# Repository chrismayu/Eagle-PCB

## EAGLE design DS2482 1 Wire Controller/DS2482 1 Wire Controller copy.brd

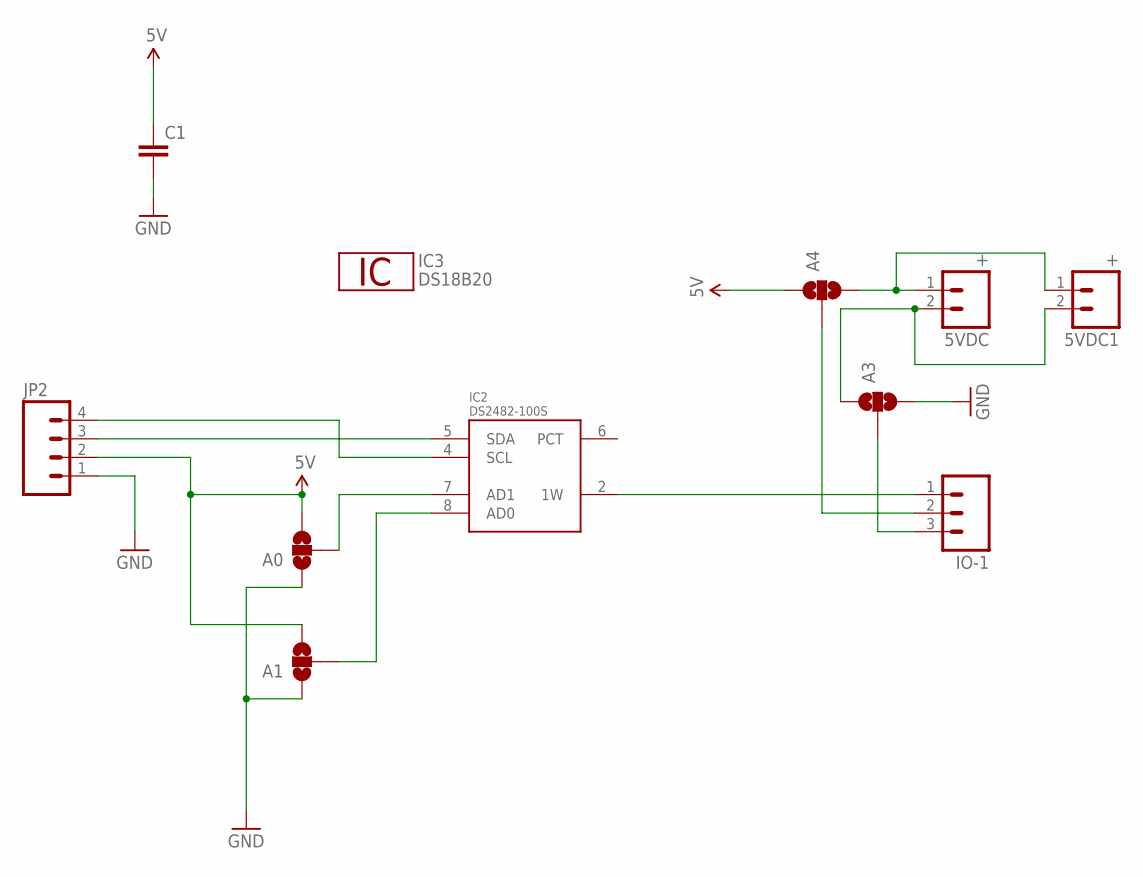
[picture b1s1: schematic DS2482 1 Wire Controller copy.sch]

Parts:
5VDC, 5VDC1: +; 1X02
A0, A1, A3, A4: SOLDERJUMPER_2WAYS; SJ_3
C1: CAPPTH2; CAP-PTH-SMALL2
IC2: DS2482-100S; SO08
IC3: DS18B20; TO92-
IO-1: M03PTH; 1X03
JP2: M04PTH; 1X04

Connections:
1W: IC3.2 (1W)
5V: A0.3, A1.3, A4.1, C1.1, JP2.2
GND: A0.1, A1.1, A3.3, C1.2, IC2.3 (GND), IC3.1 (GND), JP2.1
unnamed: IC2.2 (1W), IO-1.1
unnamed: IC2.4 (SCL), JP2.4
unnamed: A0.2, IC2.7 (AD1)
unnamed: IC2.5 (SDA), JP2.3
unnamed: A3.2, IO-1.3
unnamed: A1.2, IC2.8 (AD0)
unnamed: A4.2, IO-1.2
unnamed: 5VDC.1, 5VDC1.1, A4.3
unnamed: 5VDC.2, 5VDC1.2, A3.1
VDD: IC2.1 (VDD), IC3.3 (VDD)

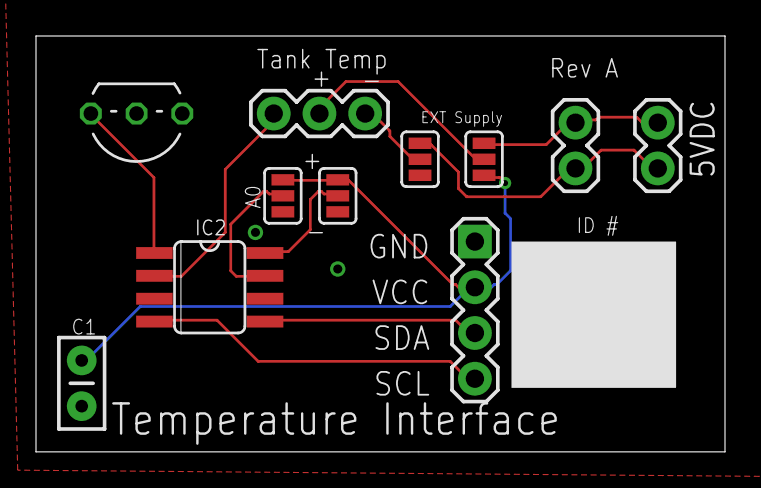
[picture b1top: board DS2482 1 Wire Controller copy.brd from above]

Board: 2 copper layers, 38.3 x 23.1 mm, 11 parts (0 on the bottom side), 12 nets.

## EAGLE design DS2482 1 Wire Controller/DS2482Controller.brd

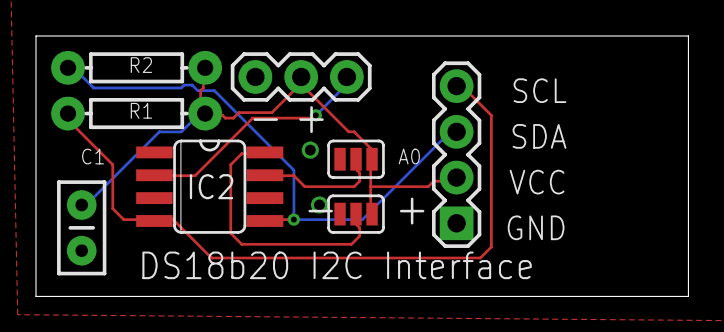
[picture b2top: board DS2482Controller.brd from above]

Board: 2 copper layers, 36.2 x 14.5 mm, 8 parts (0 on the bottom side), 7 nets.

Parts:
A0, A1: SJ_3
C1: CAP-PTH-SMALL2
IC2: DS2482-100S; SO08
JP2: 1X04
JP4: 1X03
R1, R2: 2.2k; AXIAL-0.3

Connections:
5V: A0.3, A1.3, C1.1, JP2.2, JP4.2, R1.P$2, R2.P$2
GND: A0.1, A1.1, C1.2, IC2.3, JP2.1, JP4.3
unnamed: A0.2, IC2.7
unnamed: IC2.4, JP2.4, R1.P$1
unnamed: IC2.5, JP2.3, R2.P$1
unnamed: A1.2, IC2.8
unnamed: IC2.2, JP4.1

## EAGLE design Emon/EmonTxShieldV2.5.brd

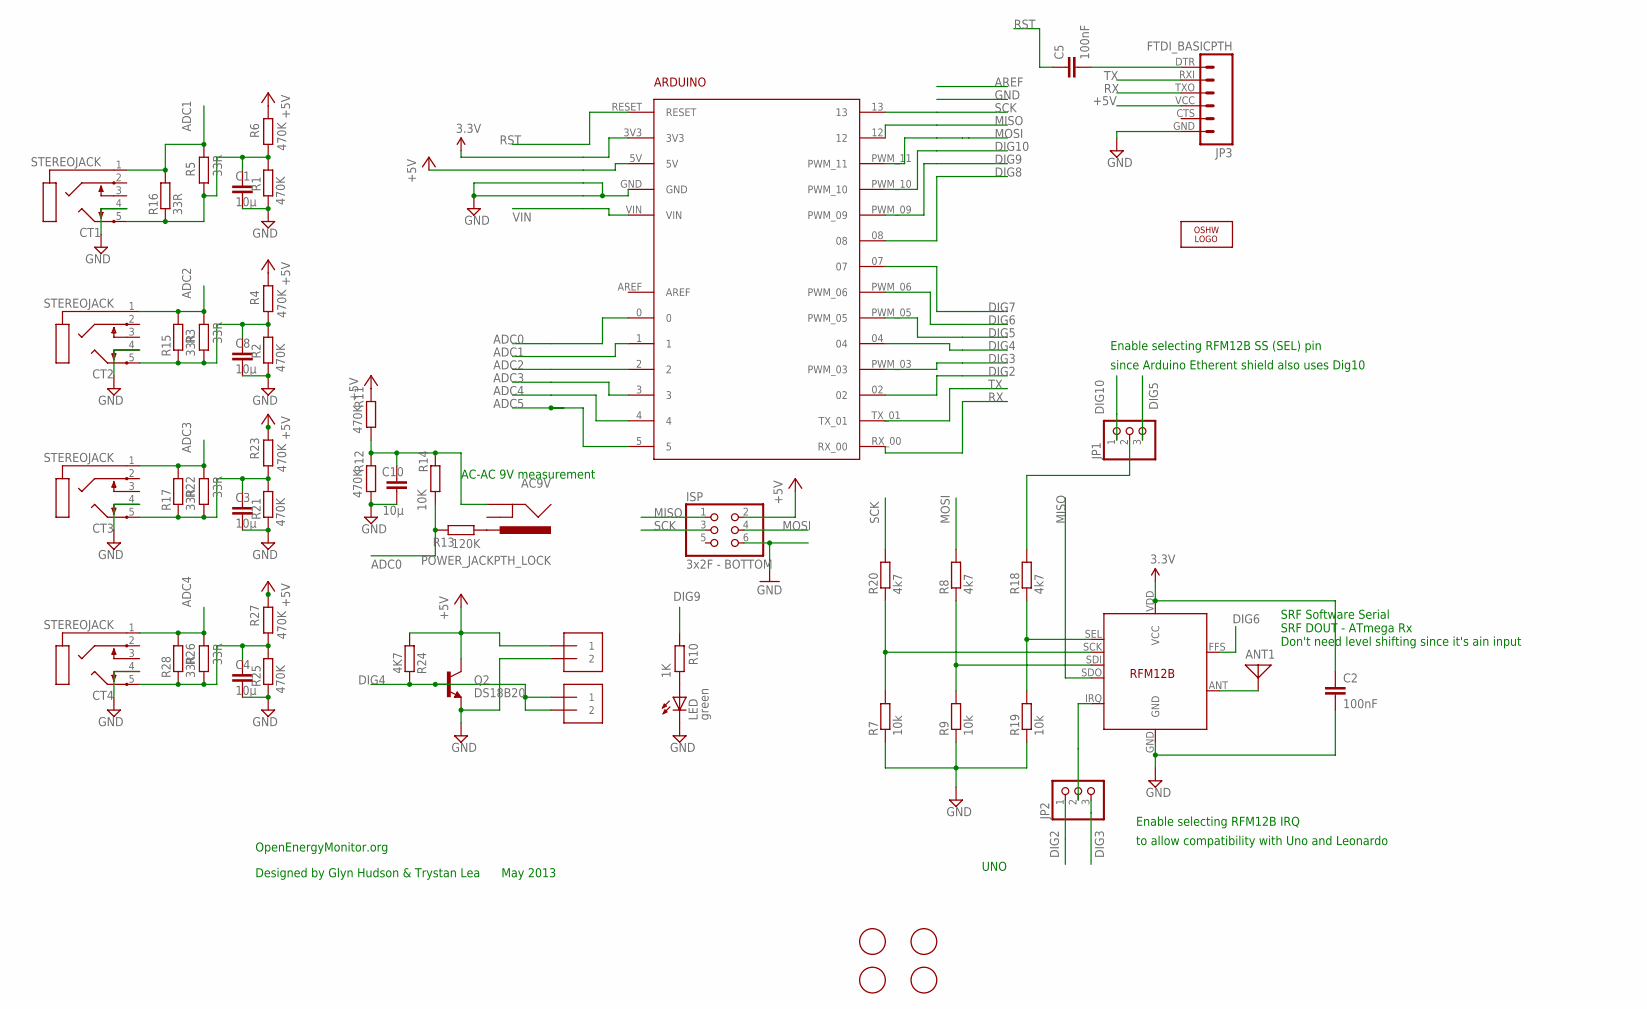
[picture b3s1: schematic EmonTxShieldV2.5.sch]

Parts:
AC9V: POWER_JACKPTH_LOCK; POWER_JACK_PTH_LOCK
ANT1: ANTENNA; PAD-01
ARDUINO1: ARDUINO2
C1, C3, C4, C8, C10: 10µ; C0603
C2, C5: 100nF; C0603
CT1, CT2, CT3, CT4: STEREOJACK; STX3100
ISP: 3x2F - BOTTOM; 2X03
J1, J2: 1X2-3.5MM
JP1, JP2: PINHD-1X3; 1X03
JP3: FTDI_BASICPTH; FTDI_BASIC
LED: green; CHIPLED_0805
LOGO1: OSHW_LOGO_10MILX0200-NT; OSHW_10X200_NOTEXT
Q2: DS18B20; TO-92
R1, R2, R4, R6, R11, R12, R21, R23, R25, R27: 470K; R0603
R3, R5, R22, R26: 33R; 0204/7
R7, R9, R19: 10k; R0603
R8, R18, R20: 4k7; R0603
R10: 1K; R0603
R13: 120K; R0603
R14: 10K; R0603
R15, R16, R17, R28: 33R; R1206
R24: 4K7; R0603
U$1, U$3, U$4, U$5: FIDUCIAL; FIDUCIAL_1MM
U$2: RFM12B

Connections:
3.3V: ARDUINO1.3V3, C2.1, U$2.VDD (VCC)
+5V: ARDUINO1.5V, ISP.2, J1.1, JP3.VCC (4), Q2.3 (C), R4.2, R6.2, R11.2, R23.2, R24.1, R27.2
ADC0: ARDUINO1.0, R13.2, R14.1
ADC1: ARDUINO1.1, CT1.1, R5.2, R16.2
ADC2: ARDUINO1.2, CT2.1, R3.2, R15.2
ADC3: ARDUINO1.3, CT3.1, R17.2, R22.2
ADC4: ARDUINO1.4, CT4.1, R26.2, R28.2
ADC5: ARDUINO1.5
DIG2: ARDUINO1.02, JP2.1
DIG3: ARDUINO1.PWM_03, JP2.3
DIG4: ARDUINO1.04, J2.1, J2.2, Q2.2 (B), R24.2
DIG5: ARDUINO1.PWM_05, JP1.3
DIG6: ARDUINO1.PWM_06, U$2.FFS
DIG7: ARDUINO1.07
DIG8: ARDUINO1.08
DIG9: ARDUINO1.PWM_09, R10.2
DIG10: ARDUINO1.PWM_10, JP1.1
GND: ARDUINO1.GND, C1.2, C2.2, C3.2, C4.2, C8.2, C10.2, CT1.4, CT2.4, CT3.4, CT4.4, ISP.6, J1.2, JP3.GND (6), LED.C, Q2.1 (E), R1.2, R2.2, R7.1, R9.1, R12.1, R19.1, R21.2, R25.2, U$2.GND
MISO: ARDUINO1.12, ISP.1, U$2.SDO
MOSI: ARDUINO1.PWM_11, ISP.4, R8.2
unnamed: JP2.2, U$2.IRQ
unnamed: JP1.2, R18.2
unnamed: C3.1, CT3.5, R17.1, R21.1, R22.1, R23.1
unnamed: C4.1, CT4.5, R25.1, R26.1, R27.1, R28.1
unnamed: AC9V.PWR, R13.1
unnamed: C5.2, JP3.DTR (1)
unnamed: C8.1, CT2.5, R2.1, R3.1, R4.1, R15.1
unnamed: AC9V.GND, C10.1, R11.1, R12.2, R14.2
unnamed: C1.1, CT1.5, R1.1, R5.1, R6.1, R16.1
unnamed: LED.A, R10.1
unnamed: ANT1.1, U$2.ANT
unnamed: R7.2, R20.1, U$2.SCK
unnamed: R8.1, R9.2, U$2.SDI
unnamed: R18.1, R19.2, U$2.SEL
RST: ARDUINO1.RESET, C5.1
RX: ARDUINO1.RX_00, JP3.TXO (3)
SCK: ARDUINO1.13, ISP.3, R20.2
TX: ARDUINO1.TX_01, JP3.RXI (2)
VIN: ARDUINO1.VIN

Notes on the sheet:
AC-AC 9V measurement
Enable selecting RFM12B SS (SEL) pin
since Arduino Etherent shield also uses Dig10
Enable selecting RFM12B IRQ
to allow compatibility with Uno and Leonardo
UNO
OpenEnergyMonitor.org
Designed by Glyn Hudson & Trystan Lea May 2013
SRF Software Serial SRF DOUT - ATmega Rx Don't need level shifting since it's ain input

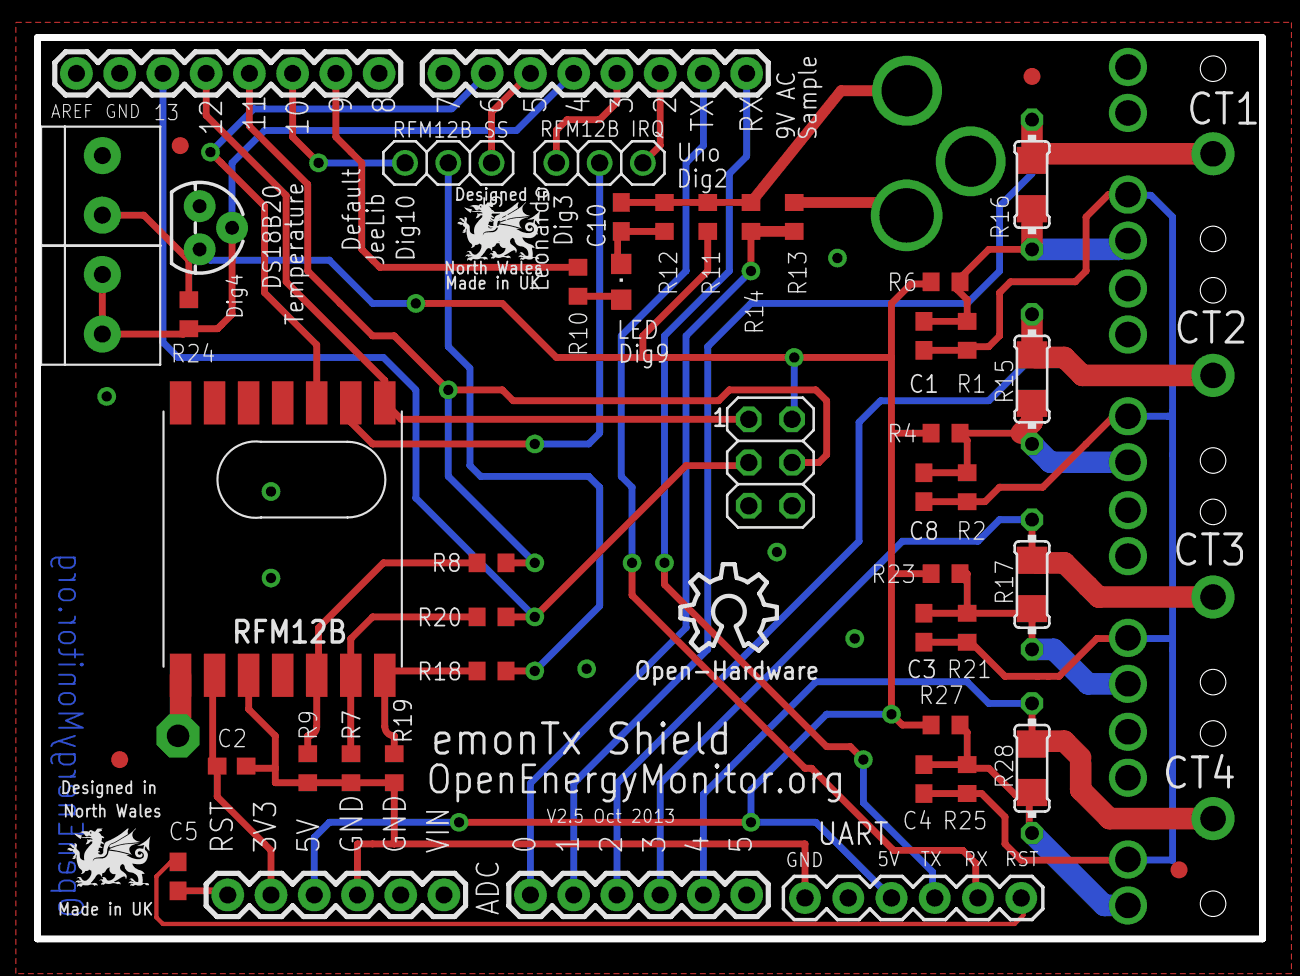
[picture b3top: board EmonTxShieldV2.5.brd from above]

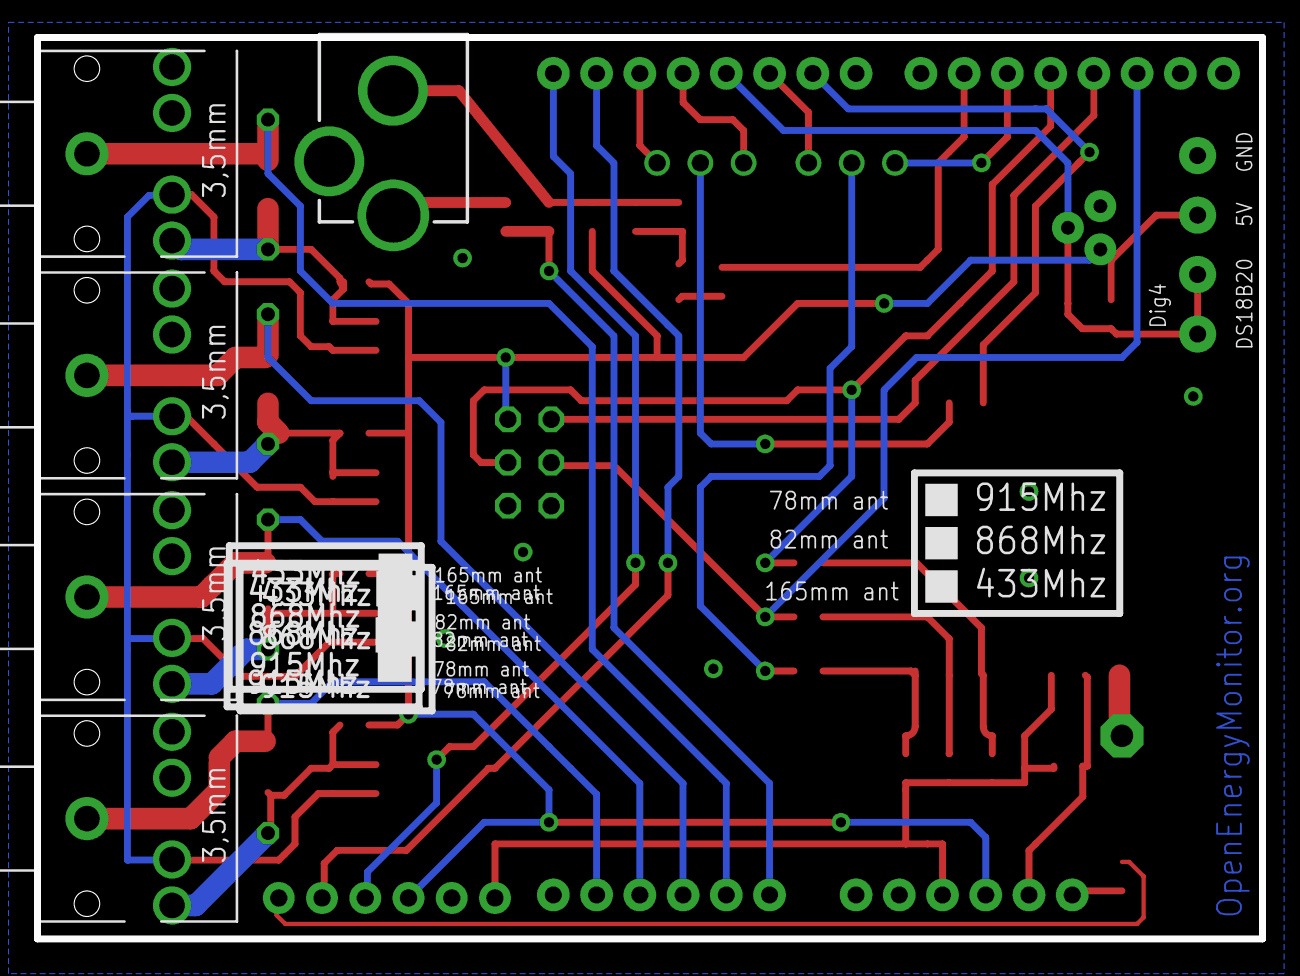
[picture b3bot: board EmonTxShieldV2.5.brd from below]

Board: 2 copper layers, 72.0 x 53.0 mm, 56 parts (5 on the bottom side), 35 nets.

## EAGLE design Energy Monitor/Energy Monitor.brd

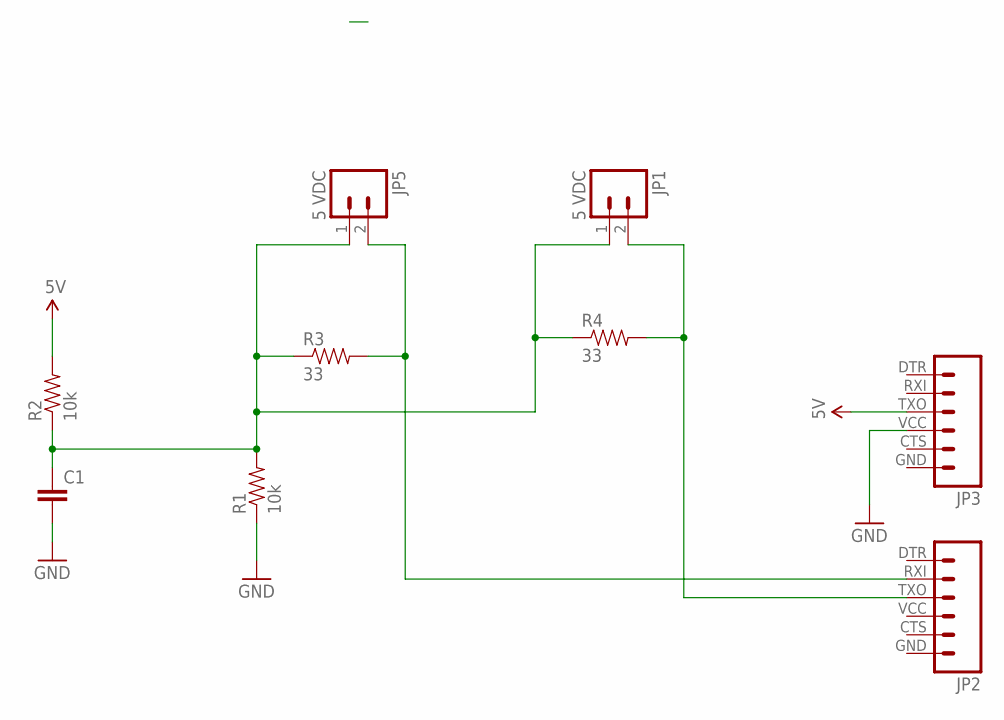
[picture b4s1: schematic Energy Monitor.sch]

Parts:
C1: CAPPTH2; CAP-PTH-SMALL2
JP1, JP5: 5 VDC; SCREWTERMINAL-5MM-2
JP2, JP3: M06SIP; 1X06
R1, R2: 10k; AXIAL-0.3
R3, R4: 33; AXIAL-0.3

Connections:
5V: JP3.TXO (3), R2.P$2 (2)
GND: C1.2, JP3.VCC (4), R1.P$1 (1)
unnamed: C1.1, JP1.1, JP5.1, R1.P$2 (2), R2.P$1 (1), R3.P$1 (1), R4.P$1 (1)
unnamed: JP1.2, JP2.TXO (3), R4.P$2 (2)
unnamed: JP2.RXI (2), JP5.2, R3.P$2 (2)

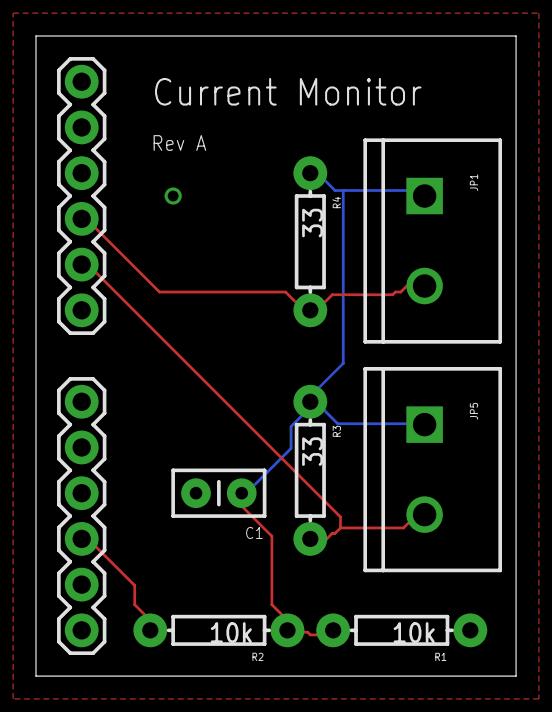
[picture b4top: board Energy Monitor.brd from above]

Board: 2 copper layers, 26.7 x 35.6 mm, 9 parts (0 on the bottom side), 5 nets.

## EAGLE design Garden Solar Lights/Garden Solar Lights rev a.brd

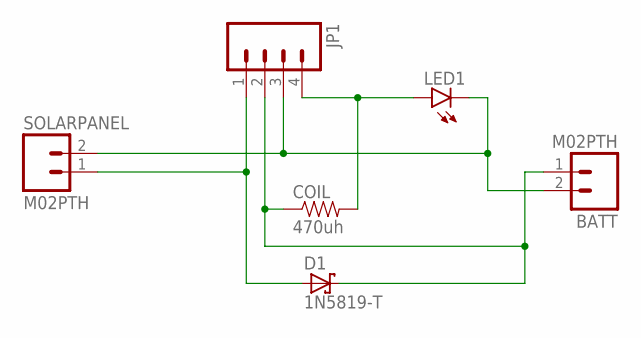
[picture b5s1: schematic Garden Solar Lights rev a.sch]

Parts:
BATT: M02PTH; 1X02
COIL: 470uh; AXIAL-0.5
D1: 1N5819-T; DO41-7.6
JP1: M04PTH; 1X04
LED1: LED3MM
SOLARPANEL: M02PTH; 1X02

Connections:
unnamed: D1.A, JP1.1, SOLARPANEL.1
unnamed: BATT.1, COIL.P$1 (1), D1.C, JP1.2
unnamed: COIL.P$2 (2), JP1.4, LED1.A
unnamed: BATT.2, JP1.3, LED1.K (C), SOLARPANEL.2

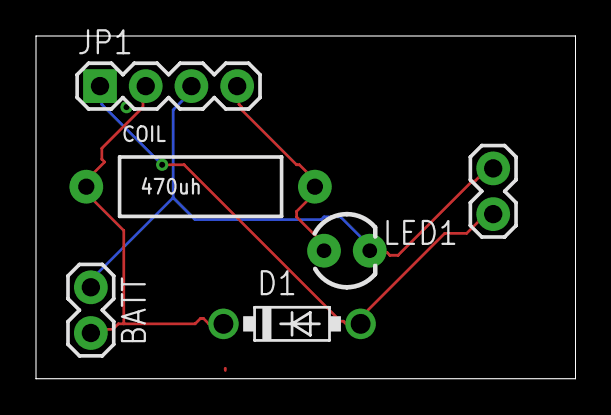
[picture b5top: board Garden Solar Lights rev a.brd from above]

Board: 2 copper layers, 30.0 x 19.0 mm, 6 parts (0 on the bottom side), 4 nets.

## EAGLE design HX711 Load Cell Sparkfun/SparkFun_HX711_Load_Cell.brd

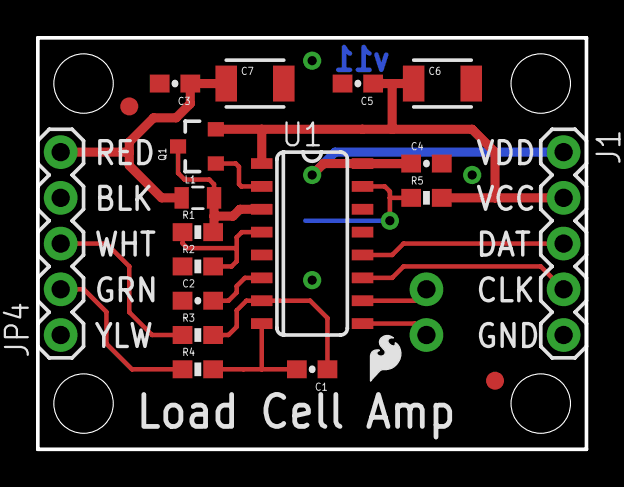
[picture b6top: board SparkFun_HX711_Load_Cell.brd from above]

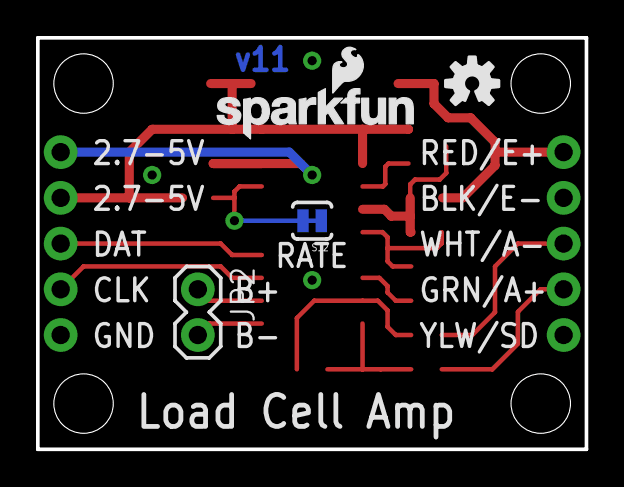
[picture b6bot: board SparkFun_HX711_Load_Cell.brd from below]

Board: 2 copper layers, 30.5 x 22.9 mm, 30 parts (4 on the bottom side), 17 nets.

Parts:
C1, C2, C3, C4, C5: 0.1uF; 0603-CAP
C6, C7: 10uF; 1210
FID1, FID2: FIDUCIAL1X2; FIDUCIAL-1X2
FRAME1: FRAME-LETTER; CREATIVE_COMMONS
J1: 1X05
JP2: 1X02
JP4: 1X05
L1: 3.3uH; 0805
LOGO1: SFE_LOGO_NAME_FLAME.1_INCH; SFE_LOGO_NAME_FLAME_.1
LOGO3: SFE_LOGO_FLAME.1_INCH; SFE_LOGO_FLAME_.1
Q1: MMBT4403; SOT23-3
R1: 20k; 0603-RES
R2: 8.2K; 0603-RES
R3, R4: 100; 0603-RES
R5: 10K; 0603-RES
SJ2: PAD-JUMPER-2-NC_BY_TRACE_YES_SILK
STANDOFF1, STANDOFF2, STANDOFF3, STANDOFF4: STAND-OFF
U1: HX711; SO16
U7: OSHW-LOGOS; OSHW-LOGO-S
U$1: REVISION

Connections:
A+: JP4.2, R4.1
A-: JP4.3, R3.1
AVDD: C3.1, C7.1, JP4.5, L1.1
B+: JP2.1, U1.10
B-: JP2.2, U1.9
DAT: J1.3, U1.12
GND: C2.1, C3.2, C4.2, C5.2, C6.2, C7.2, J1.5, JP4.1, JP4.4, R2.1, SJ2.1, U1.5, U1.14
unnamed: R5.1, SJ2.2, U1.15
unnamed: C1.1, R3.2, U1.7
unnamed: C1.2, R4.2, U1.8
unnamed: Q1.1, U1.2
unnamed: L1.2, Q1.3, R1.2, U1.3
unnamed: R1.1, R2.2, U1.4
unnamed: C2.2, U1.6
SCK: J1.4, U1.11
VCC: C5.1, C6.1, J1.2, Q1.2, R5.2, U1.1
VDD: C4.1, J1.1, U1.16

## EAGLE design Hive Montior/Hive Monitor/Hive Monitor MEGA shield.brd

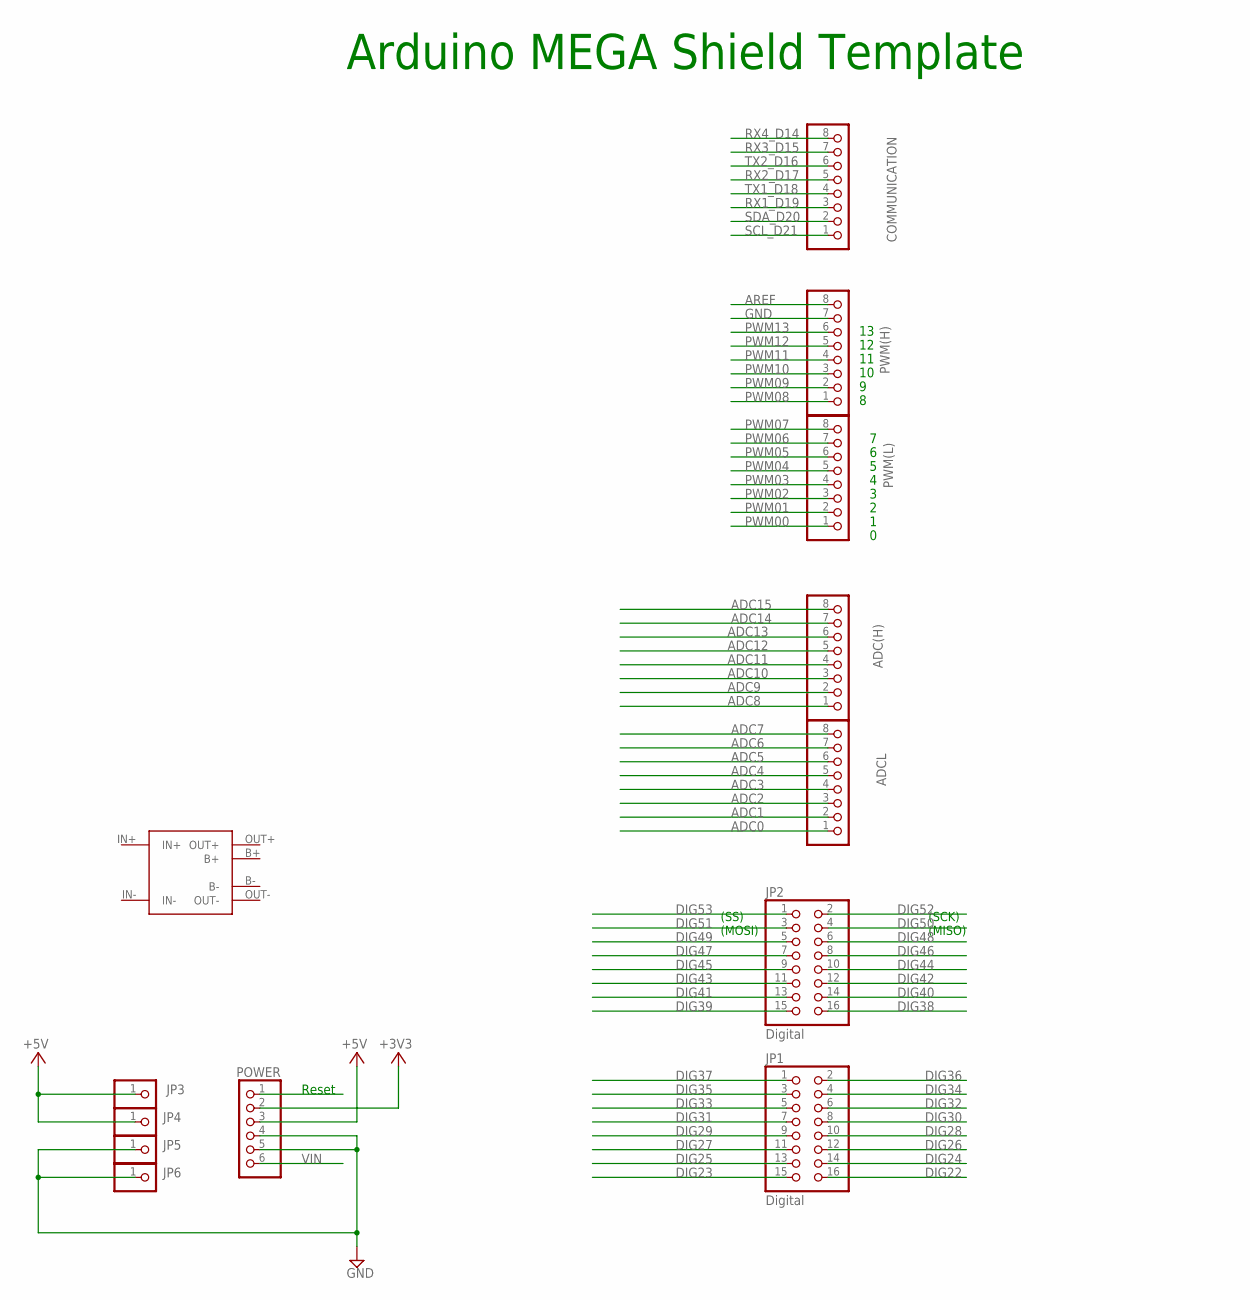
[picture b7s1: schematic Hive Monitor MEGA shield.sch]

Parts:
ADC(H): PINHD-1X8; 1X08
ADCL: PINHD-1X8; 1X08
COMMUNICATION: PINHD-1X8; 1X08
JP1, JP2: Digital; 2X08
JP3, JP4, JP5, JP6: PINHD-1X1; 1X01
POWER: PINHD-1X6; 1X06
PWM(H): PINHD-1X8; 1X08
PWM(L): PINHD-1X8; 1X08
U$1: TP4056-MODULE; TP4056-LITHIUM-PROTECTED-MODULE

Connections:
+3V3: POWER.2
+5V: JP3.1, JP4.1, POWER.3
ADC0: ADCL.1
ADC1: ADCL.2
ADC2: ADCL.3
ADC3: ADCL.4
ADC4: ADCL.5
ADC5: ADCL.6
ADC6: ADCL.7
ADC7: ADCL.8
ADC8: ADC(H).1
ADC9: ADC(H).2
ADC10: ADC(H).3
ADC11: ADC(H).4
ADC12: ADC(H).5
ADC13: ADC(H).6
ADC14: ADC(H).7
ADC15: ADC(H).8
AREF: PWM(H).8
B+: U$1.B+
B-: U$1.B-
DIG22: JP1.16
DIG23: JP1.15
DIG24: JP1.14
DIG25: JP1.13
DIG26: JP1.12
DIG27: JP1.11
DIG28: JP1.10
DIG29: JP1.9
DIG30: JP1.8
DIG31: JP1.7
DIG32: JP1.6
DIG33: JP1.5
DIG34: JP1.4
DIG35: JP1.3
DIG36: JP1.2
DIG37: JP1.1
DIG38: JP2.16
DIG39: JP2.15
DIG40: JP2.14
DIG41: JP2.13
DIG42: JP2.12
DIG43: JP2.11
DIG44: JP2.10
DIG45: JP2.9
DIG46: JP2.8
DIG47: JP2.7
DIG48: JP2.6
DIG49: JP2.5
DIG50: JP2.4
DIG51: JP2.3
DIG52: JP2.2
DIG53: JP2.1
GND: JP5.1, JP6.1, POWER.4, POWER.5, PWM(H).7
IN+: U$1.IN+
IN-: U$1.IN-
OUT+: U$1.OUT+
OUT-: U$1.OUT-
PWM00: PWM(L).1
PWM01: PWM(L).2
PWM02: PWM(L).3
PWM03: PWM(L).4
PWM04: PWM(L).5
PWM05: PWM(L).6
PWM06: PWM(L).7
PWM07: PWM(L).8
PWM08: PWM(H).1
PWM09: PWM(H).2
PWM10: PWM(H).3
PWM11: PWM(H).4
PWM12: PWM(H).5
PWM13: PWM(H).6
RESET: POWER.1
RX1_D19: COMMUNICATION.3
RX2_D17: COMMUNICATION.5
RX3_D15: COMMUNICATION.7
RX4_D14: COMMUNICATION.8
SCL_D21: COMMUNICATION.1
SDA_D20: COMMUNICATION.2
TX1_D18: COMMUNICATION.4
TX2_D16: COMMUNICATION.6
VIN: POWER.6

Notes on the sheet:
Arduino MEGA Shield Template
(SS)
(MOSI)
(SCK)
(MISO)
Reset

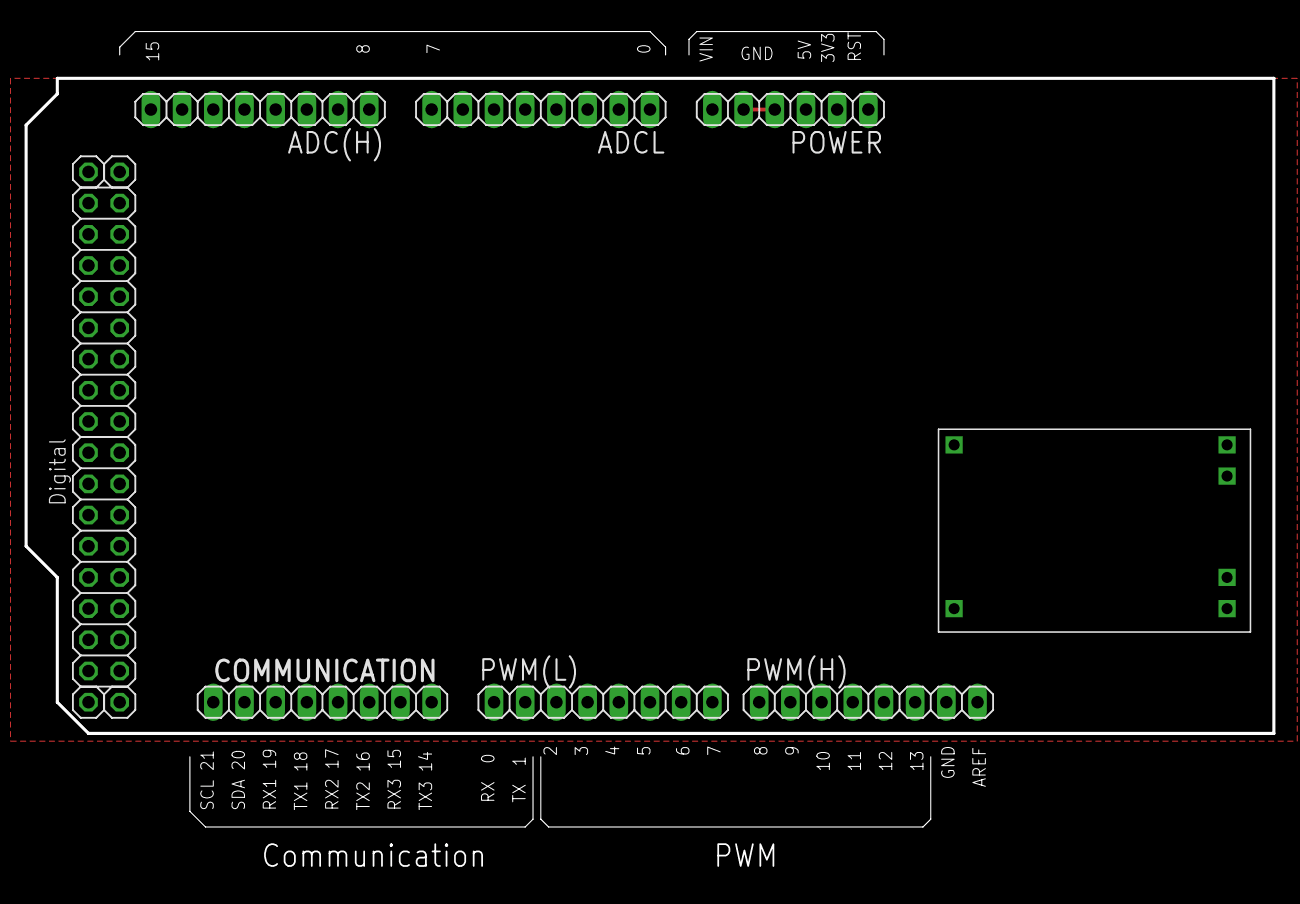
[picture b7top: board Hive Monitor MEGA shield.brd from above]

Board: 2 copper layers, 101.6 x 53.3 mm, 13 parts (0 on the bottom side), 2 nets.

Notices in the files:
parts and their libraries:
SparkFun-Capacitors: Licensing: Creative Commons ShareAlike 4.0 International - https://creativecommons.org/licenses/by-sa/4.0
SparkFun-Connectors: Licensing: CC v3.0 Share-Alike You are welcome to use this library for commercial purposes.
